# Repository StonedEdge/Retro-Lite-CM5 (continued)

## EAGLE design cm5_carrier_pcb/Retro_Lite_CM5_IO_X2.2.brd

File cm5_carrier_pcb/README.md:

# Retro Lite CM5 Carrier Board v1.1 

## What is this folder?
Note: The current files are now tested and verified to work with Radxa v2.2 carrier boards. **Also now verified to work Radxa V2.21 boards!**

This folder contains the BOM, EAGLE schematic (.sch) and board (.brd) files, as well as pick & place files to order the board with JLCPCB or your fab of choice. 
The main carrier board is a 6-layer board and you should order the board with impedance matching, according to the JLC06081H-2116 (Standard) stackup offering (0.8mm thickness). 
Currently, this version is only compatible with the Radxa CM5 (version X2.2/X2.21) & I have not tested it with other SoMs, like the Raspberry Pi CM4. 

Expect to pay around $250 per board to have it fabbed and turnkeyed with JLCPCB.

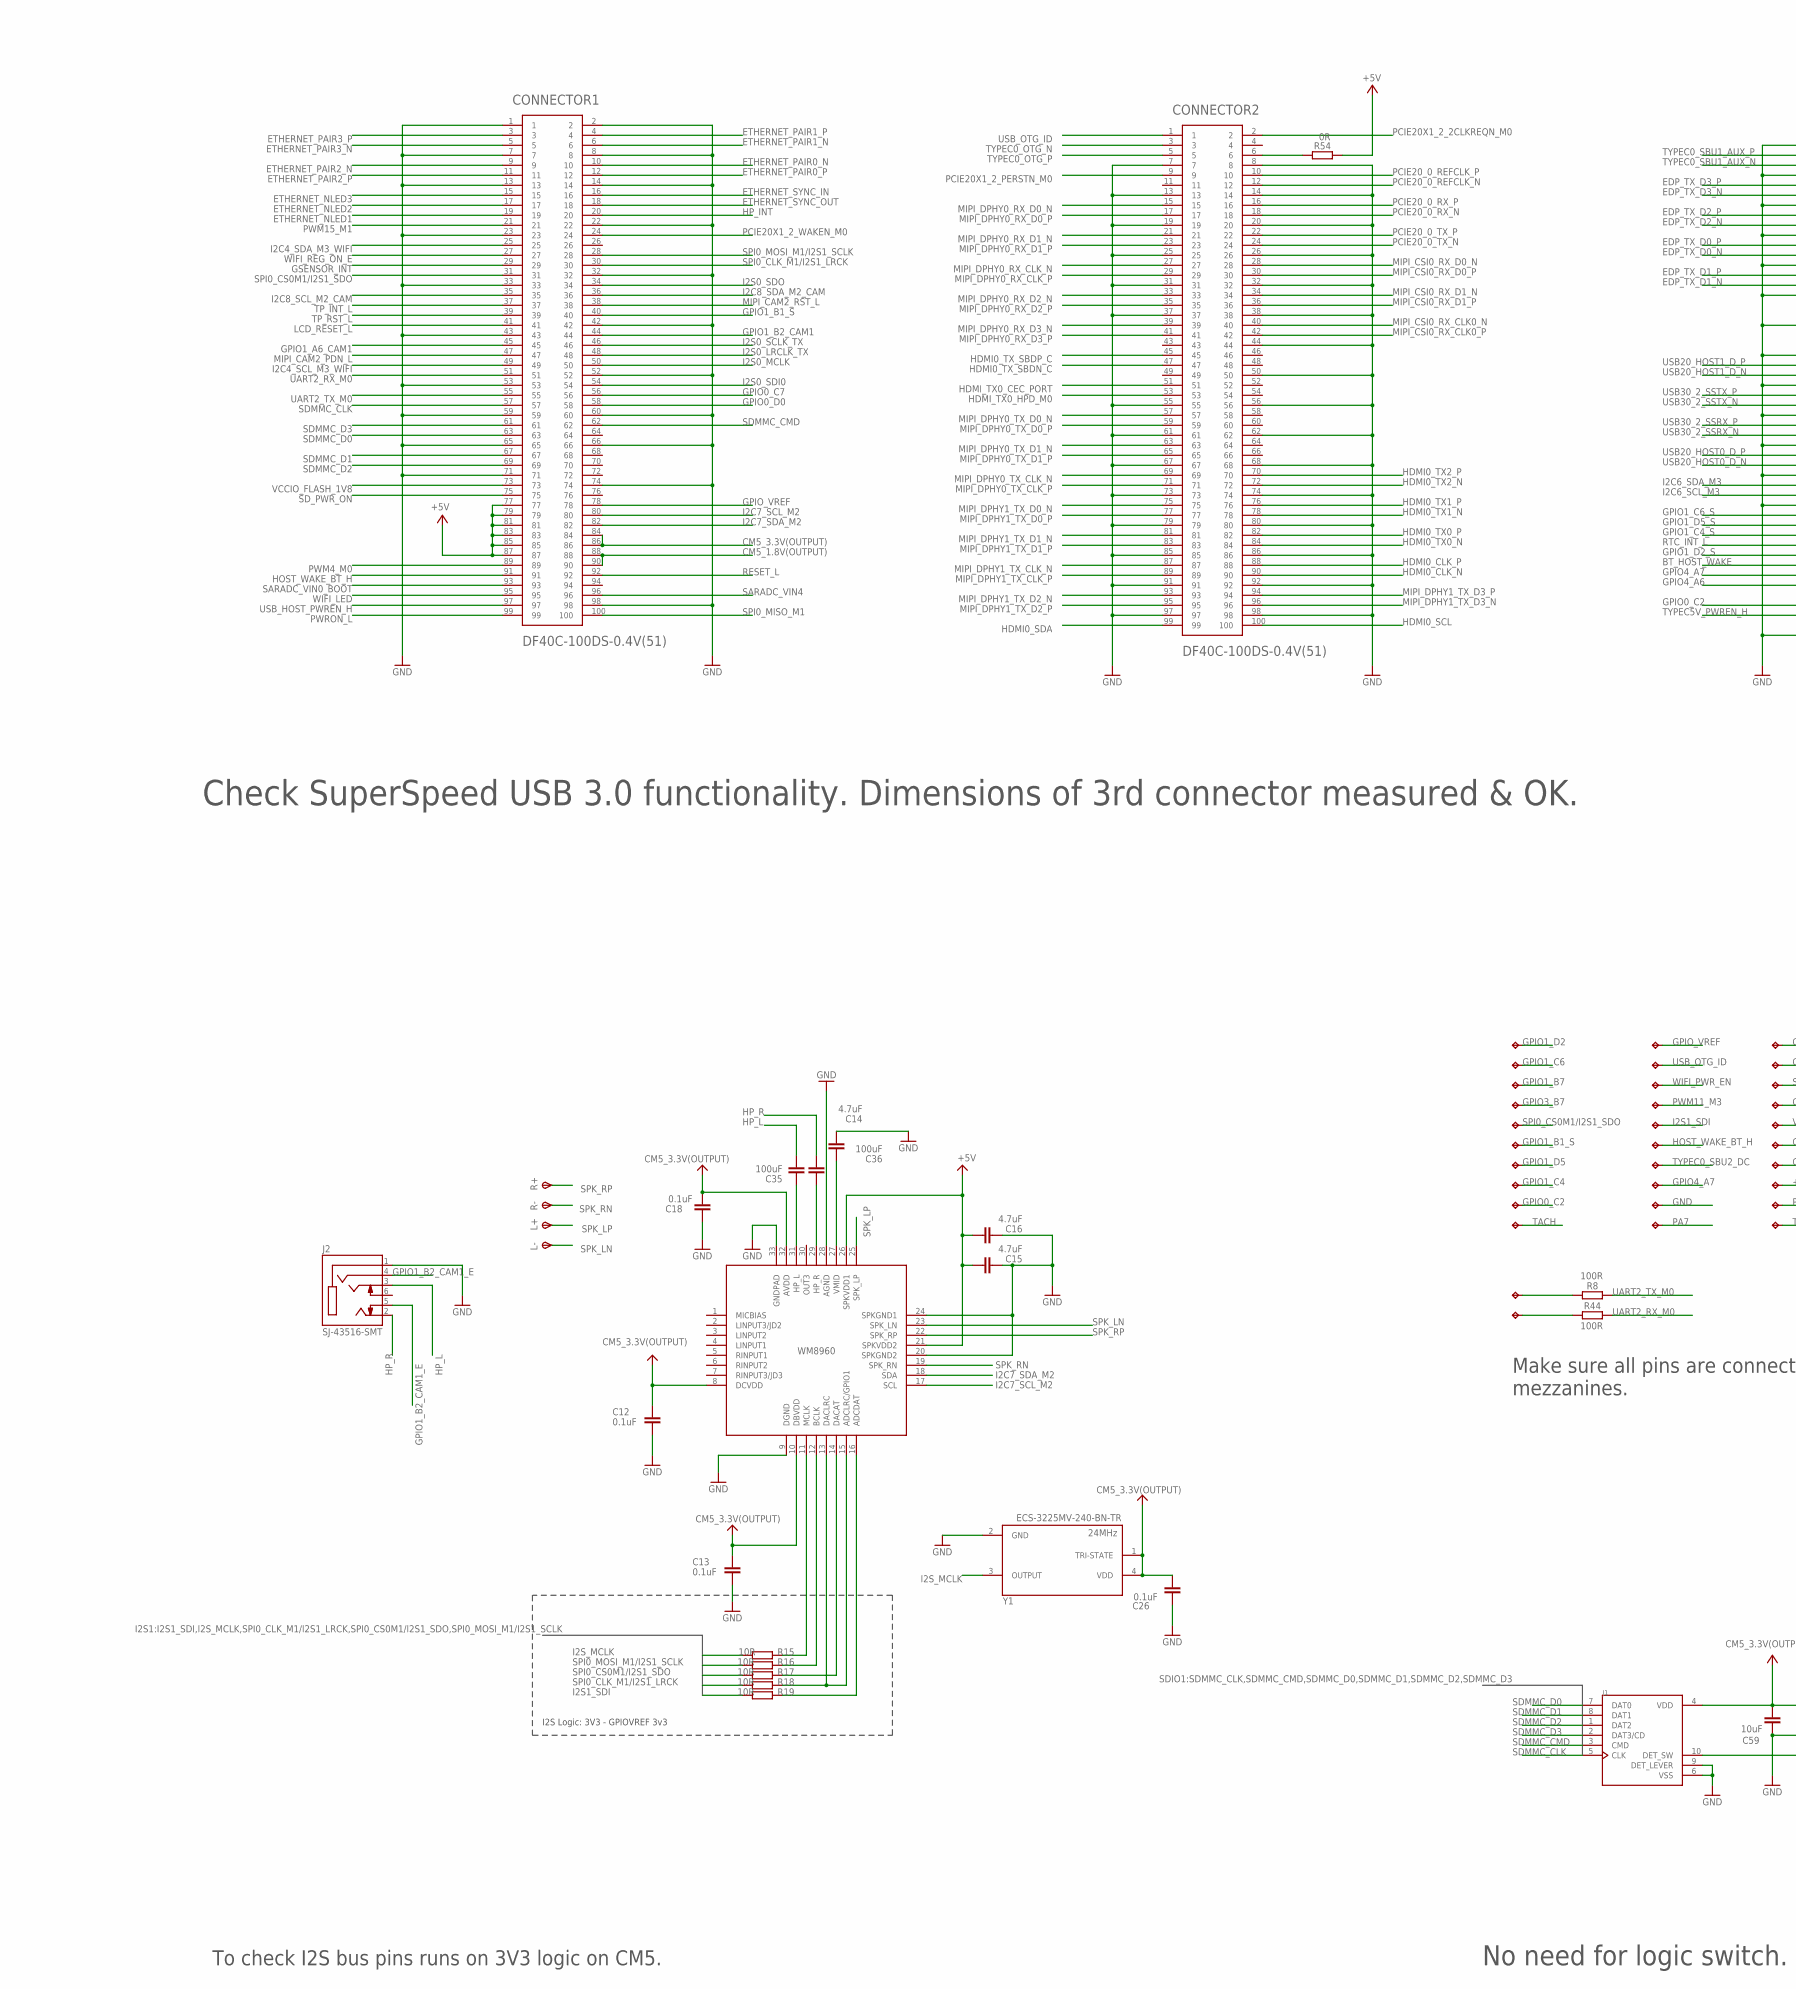
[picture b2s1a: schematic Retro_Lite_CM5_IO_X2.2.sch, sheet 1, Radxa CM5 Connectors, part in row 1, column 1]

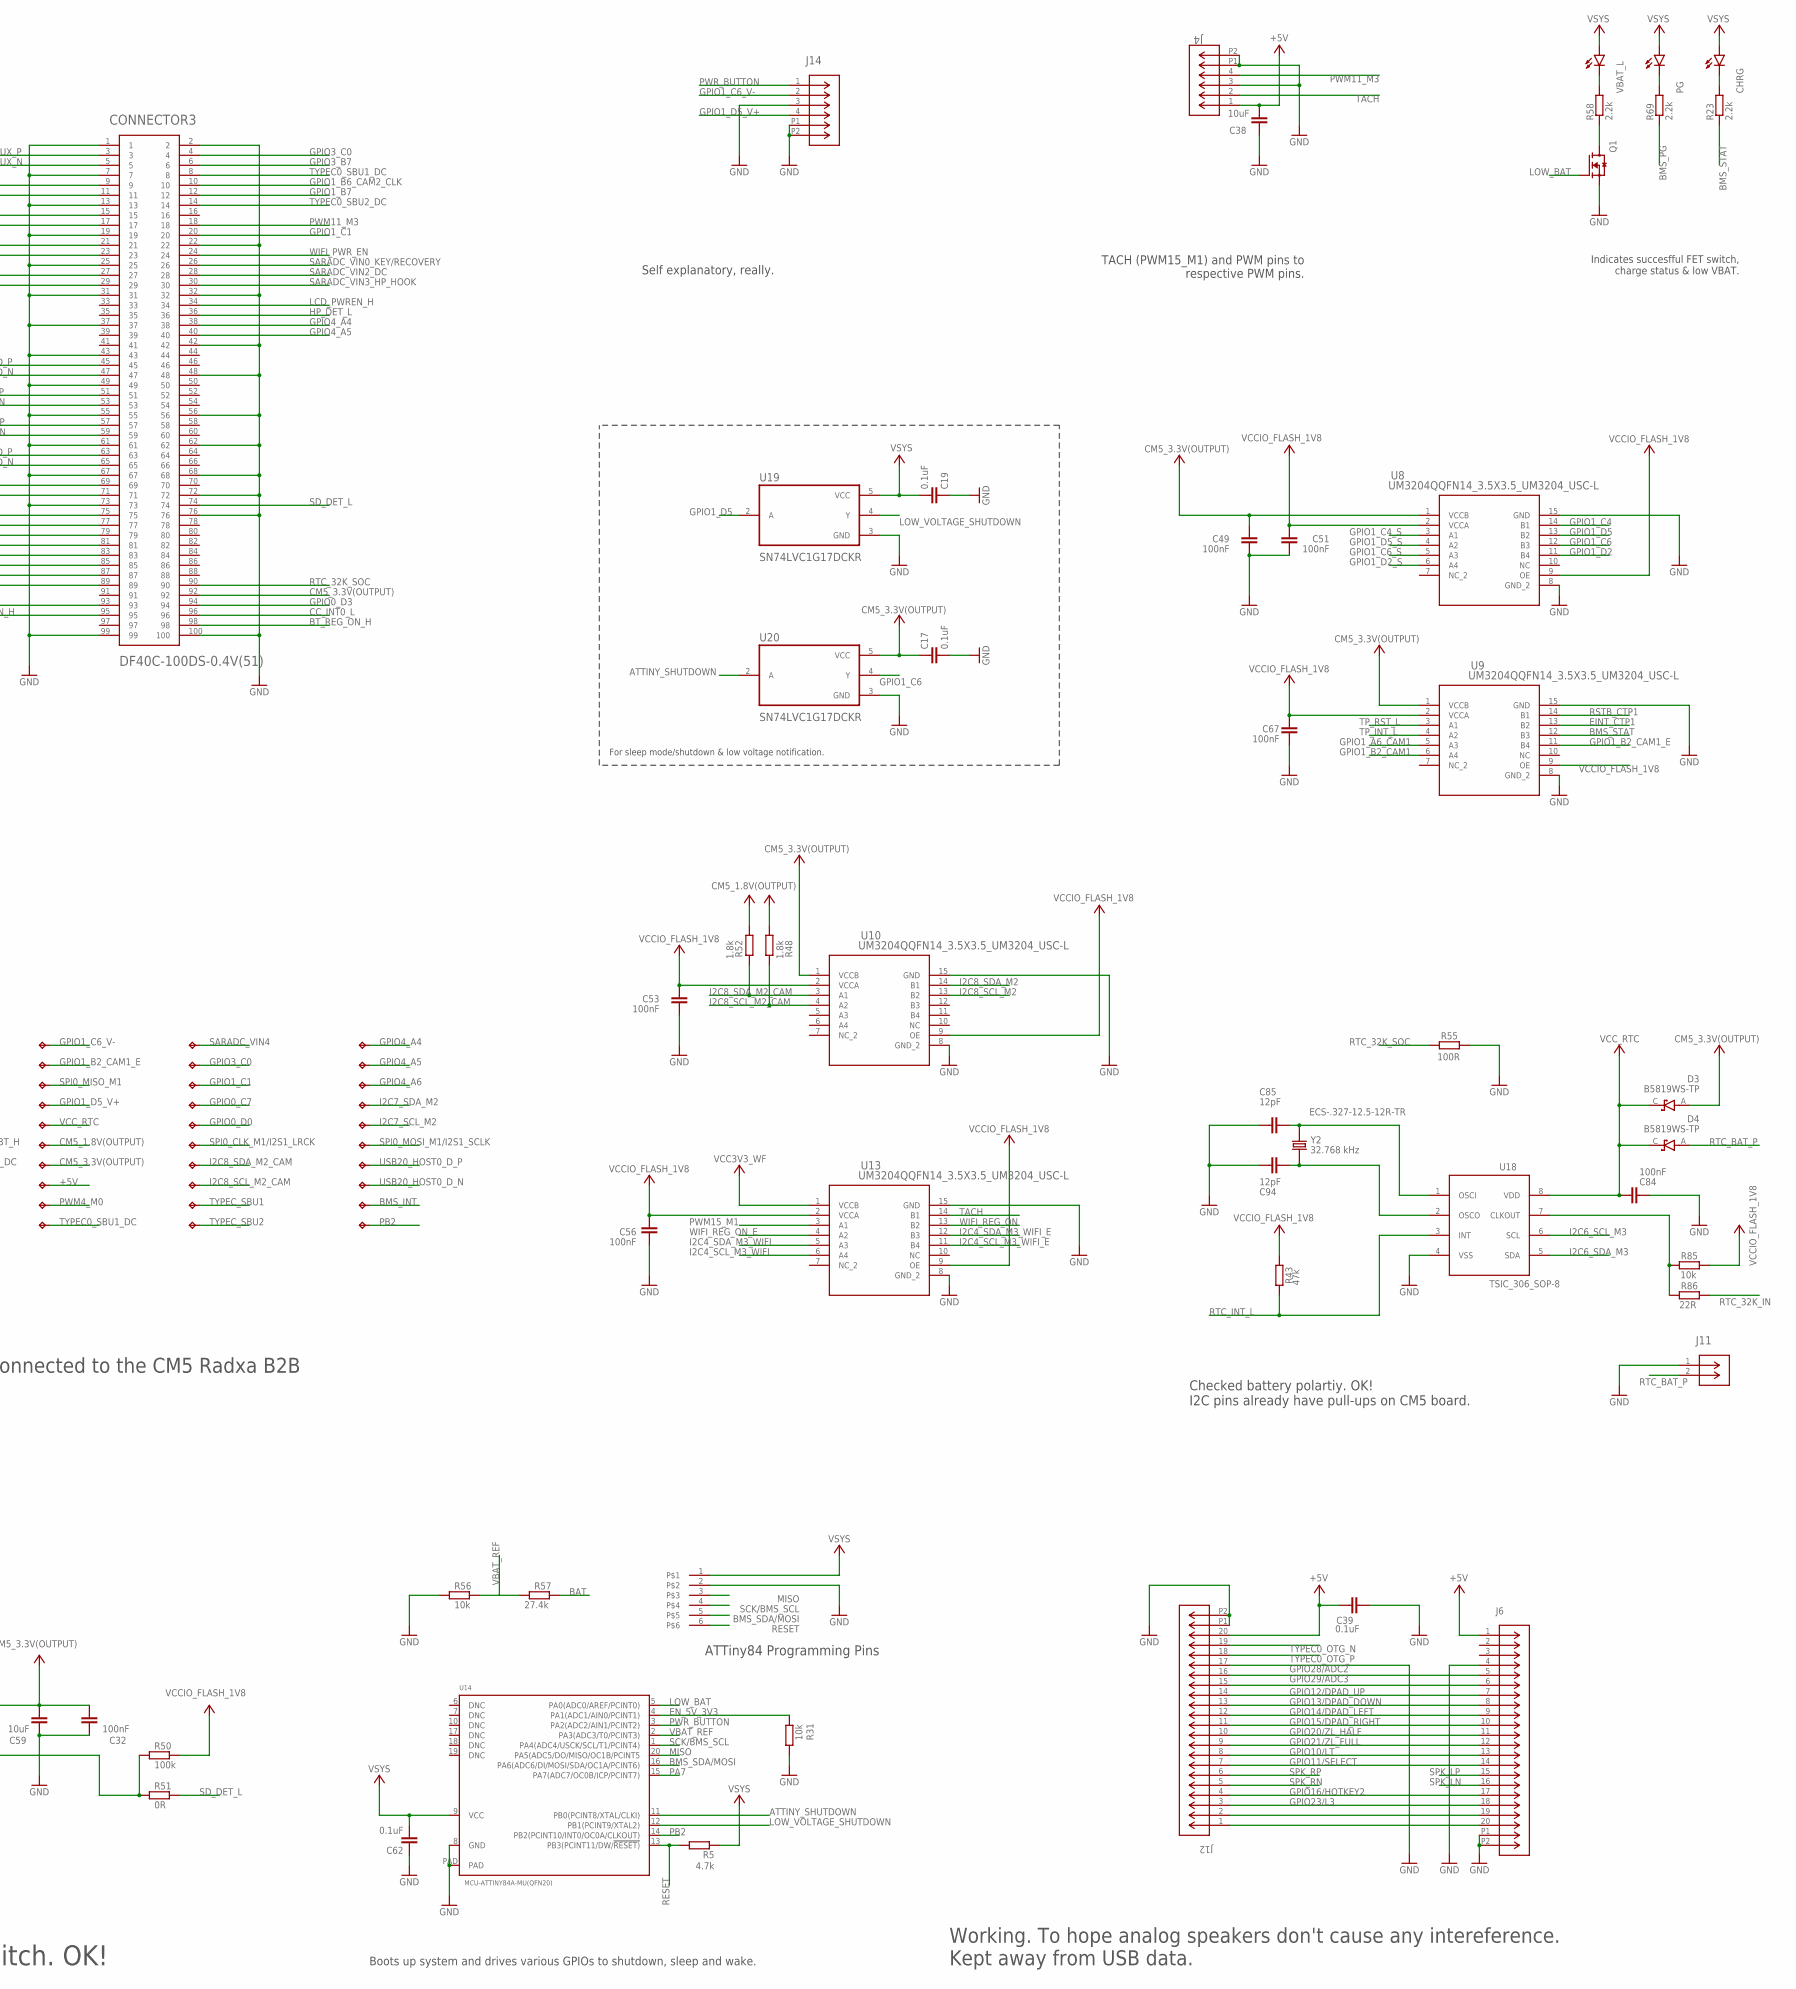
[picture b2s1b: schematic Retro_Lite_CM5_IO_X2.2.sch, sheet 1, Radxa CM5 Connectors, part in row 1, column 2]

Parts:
1V8_SCL, 1V8_SDA, 3V3_SCL, 3V3_SDA: TPTP07R; TP07R
+5V: TPTP07R; TP07R
BMS_INT: TPTP07R; TP07R
BT_DIS: TPTP07R; TP07R
C12, C13, C18, C26: 0.1uF; C0603
C14, C15, C16: 4.7uF; C0603
C17, C19, C39, C62: 0.1uF; C0402
C32, C49, C51, C53, C56, C67, C84, C94: 100nF; C0402
C35, C36: 100uF; C1206
C38: 10uF; 0805
C59: 10uF; C0402
C85: 12pF; C0402
CHRG: LEDSML0603; SML0603
CM5_1V8, CM5_3.3V: TPTP07R; TP07R
CONNECTOR1, CONNECTOR2, CONNECTOR3: DF40C-100DS-0.4V(51); HRS_DF40C-100DS-0.4V(51)
D3, D4: B5819WS-TP; SOD2512X115N
GND: TPTP07R; TP07R
GPIO0_C2, GPIO0_C7, GPIO0_D0, GPIO1_B1, GPIO1_B7, GPIO1_C1, GPIO1_C4, GPIO1_C6, GPIO1_C6_V-, GPIO1_D2, GPIO1_D5, GPIO1_D5_V+, GPIO3_B7, GPIO3_C0, GPIO4_A4, GPIO4_A5, GPIO4_A6, GPIO4_A7, GPIO14_HPD: TPTP07R; TP07R
GPIO_VREF: TPTP07R; TP07R
I2S1_LRCK, I2S1_SCLK, I2S1_SDI, I2S1_SDO: TPTP07R; TP07R
J1: 5025700893; MOLEX_5025700893
J2: SJ-43516-SMT; CUI_SJ-43516-SMT
J4, J14: 5051100492; CON_5051100492_MOL
J6, J12: 5034802000; CON_5034802000_MOL
J11: 1072TR; CONN_1072TR_KEY
L+: TPSTP09SQ; TP09SQ
L-: TPSTP09SQ; TP09SQ
NEXTRST: TPTP07R; TP07R
PB0, PB1: TPTP07R; TP07R
PG: LEDSML0603; SML0603
PWM_CTRL: TPTP07R; TP07R
Q1: AO3400A; SOT95P280X125-3N
R5: 4.7k; R0402
R8, R44, R55: 100R; R0402
R15, R16, R17, R18, R19: 10R; R0603
R23, R58, R69: 2.2k; R0402
R31, R56, R85: 10k; R0402
R43: 47k; R0402
R48, R52: 1.8k; R0402
R50: 100k; R0402
R51, R54: 0R; R0402
R57: 27.4k; R0402
R86: 22R; R0402
R+: TPSTP09SQ; TP09SQ
R-: TPSTP09SQ; TP09SQ
SARADC_VIN4: TPTP07R; TP07R
SBU1, SBU1_DC, SBU2, SBU2_DC: TPTP07R; TP07R
TACH: TPTP07R; TP07R
U6: WM8960; QFN50P500X500X100-33N
U8, U9, U10, U13: UM3204QQFN14_3.5X3.5_UM3204_USC-L; QFN14_3.5X3.5_UM3204_USC-L
U14: MCU-ATTINY84A-MU(QFN20); QFN20G-0.5-4X4MM
U18: TSIC_306_SOP-8; SOIC127P602X173-8N
U19, U20: SN74LVC1G17DCKR; SOT65P210X110-5N
U$3: 6PINEADER; 1MM_PIC-PROGRAMING_HEADER
UART2_RX_M0, UART2_TX_M0: TPTP07R; TP07R
USB20_HOST0_N, USB20_HOST0_P: TPTP07R; TP07R
USB_OTG_ID: TPTP07R; TP07R
VBAT_L: LEDSML0603; SML0603
VCC_RTC: TPTP07R; TP07R
WIFI_PWR_EN: TPTP07R; TP07R
WL_DIS/PWM4_M0: TPTP07R; TP07R
Y1: ECS-3225MV-240-BN-TR; OSC_ECS-2333-160-BN-TR
Y2: ECS-.327-12.5-12R-TR; XTAL_ECS-.327-12.5-12R-TR

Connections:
3V3: J6.19, J12.2
+5V: +5V.TP, C15.1, C16.1, C38.2, C39.1, CONNECTOR1.77, CONNECTOR1.79, CONNECTOR1.81, CONNECTOR1.83, CONNECTOR1.85, CONNECTOR1.87, J4.1, J6.1, J12.20, R54.2, U6.21 (SPKVDD2), U6.26 (SPKVDD1); also elsewhere on the board
ADC: R19.2, U6.16 (ADCDAT)
ATTINY_SHUTDOWN: U14.11 (PB0(PCINT8/XTAL/CLKI)), U20.2 (A)
BAT: R57.2; also elsewhere on the board
BCLK: R16.2, U6.12 (BCLK)
BMS_INT: BMS_INT.TP; also elsewhere on the board
BMS_PG: R69.1
BMS_SDA/MOSI: U14.16 (PA6(ADC6/DI/MOSI/SDA/OC1A/PCINT6)), U$3.5; also elsewhere on the board
BMS_STAT: R23.1, U9.12 (B3); also elsewhere on the board
BT_HOST_WAKE: CONNECTOR3.85; also elsewhere on the board
BT_REG_ON_H: CONNECTOR3.98; also elsewhere on the board
CC_INT0_L: CONNECTOR3.96
CM5_1.8V(OUTPUT): CM5_1V8.TP, CONNECTOR1.88, CONNECTOR1.90, R48.2, R52.2; also elsewhere on the board
CM5_3.3V(OUTPUT): C12.1, C13.1, C17.1, C18.2, C26.2, C32.2, C49.2, C59.2, CM5_3.3V.TP, CONNECTOR1.84, CONNECTOR1.86, CONNECTOR3.92, D3.A, J1.4 (VDD), U6.8 (DCVDD), U6.10 (DBVDD), U6.32 (AVDD), U8.1 (VCCB), U9.1 (VCCB), U10.1 (VCCB), U20.5 (VCC), Y1.1 (TRI-STATE), Y1.4 (VDD); also elsewhere on the board
DAC: R17.2, U6.14 (DACAT)
EDP_TX_D0_N: CONNECTOR3.23; also elsewhere on the board
EDP_TX_D0_P: CONNECTOR3.21; also elsewhere on the board
EDP_TX_D1_N: CONNECTOR3.29; also elsewhere on the board
EDP_TX_D1_P: CONNECTOR3.27; also elsewhere on the board
EDP_TX_D2_N: CONNECTOR3.17; also elsewhere on the board
EDP_TX_D2_P: CONNECTOR3.15; also elsewhere on the board
EDP_TX_D3_N: CONNECTOR3.11; also elsewhere on the board
EDP_TX_D3_P: CONNECTOR3.9; also elsewhere on the board
EINT_CTP1: U9.13 (B2); also elsewhere on the board
EN_5V_3V3: R31.2, U14.4 (PA1(ADC1/AIN0/PCINT1)); also elsewhere on the board
ETHERNET_NLED1: CONNECTOR1.19
ETHERNET_NLED2: CONNECTOR1.17
ETHERNET_NLED3: CONNECTOR1.15
ETHERNET_PAIR0_N: CONNECTOR1.10
ETHERNET_PAIR0_P: CONNECTOR1.12
ETHERNET_PAIR1_N: CONNECTOR1.6
ETHERNET_PAIR1_P: CONNECTOR1.4
ETHERNET_PAIR2_N: CONNECTOR1.9
ETHERNET_PAIR2_P: CONNECTOR1.11
ETHERNET_PAIR3_N: CONNECTOR1.5
ETHERNET_PAIR3_P: CONNECTOR1.3
ETHERNET_SYNC_IN: CONNECTOR1.16
ETHERNET_SYNC_OUT: CONNECTOR1.18
GND: C12.2, C13.2, C14.2, C15.2, C16.2, C17.2, C18.1, C19.1, C26.1, C32.1, C38.1, C39.2, C49.1, C51.1, C53.1, C56.1, C59.1, C62.1, C67.1, C84.1, C85.2, C94.2, CONNECTOR1.1, CONNECTOR1.2, CONNECTOR1.7, CONNECTOR1.8, CONNECTOR1.13, CONNECTOR1.14, CONNECTOR1.22, CONNECTOR1.23, CONNECTOR1.32, CONNECTOR1.33, CONNECTOR1.42, CONNECTOR1.43, CONNECTOR1.52, CONNECTOR1.53, CONNECTOR1.59, CONNECTOR1.60, CONNECTOR1.65, CONNECTOR1.66, CONNECTOR1.71, CONNECTOR1.74, CONNECTOR1.98, CONNECTOR2.7, CONNECTOR2.8, CONNECTOR2.13, CONNECTOR2.14, CONNECTOR2.19, CONNECTOR2.20, CONNECTOR2.25, CONNECTOR2.26, CONNECTOR2.31, CONNECTOR2.32, CONNECTOR2.37, CONNECTOR2.38, CONNECTOR2.44, CONNECTOR2.50, CONNECTOR2.55, CONNECTOR2.56, CONNECTOR2.61, CONNECTOR2.62, CONNECTOR2.67, CONNECTOR2.68, CONNECTOR2.73, CONNECTOR2.74, CONNECTOR2.79, CONNECTOR2.80, CONNECTOR2.85, CONNECTOR2.86, CONNECTOR2.91, CONNECTOR2.92, CONNECTOR2.97, CONNECTOR2.98, CONNECTOR3.1, CONNECTOR3.2, CONNECTOR3.7, CONNECTOR3.13, CONNECTOR3.19, CONNECTOR3.22, CONNECTOR3.25, CONNECTOR3.31, CONNECTOR3.32, CONNECTOR3.37, CONNECTOR3.42, CONNECTOR3.43, CONNECTOR3.48, CONNECTOR3.49, CONNECTOR3.55, CONNECTOR3.56, CONNECTOR3.61, CONNECTOR3.62, CONNECTOR3.67, CONNECTOR3.68, CONNECTOR3.72, CONNECTOR3.73, CONNECTOR3.76, CONNECTOR3.99, CONNECTOR3.100, GND.TP, J1.6 (VSS), J1.9 (DET_LEVER), J2.1 (SLEEVE), J4.3, J4.P1, J4.P2, J6.4, J6.P1, J6.P2, J11.1, J12.17, J12.P1, J12.P2, J14.3, J14.P1, J14.P2, Q1.2 (S), R31.1, R55.2, R56.1, U6.9 (DGND), U6.20 (SPKGND2), U6.24 (SPKGND1), U6.28 (AGND), U6.33 (GNDPAD), U8.8 (GND_2), U8.15 (GND), U9.8 (GND_2), U9.15 (GND), U10.8 (GND_2), U10.15 (GND), U13.8 (GND_2), U13.15 (GND), U14.8 (GND), U14.PAD, U18.4 (VSS), U19.3 (GND), U20.3 (GND), U$3.2, Y1.2 (GND); also elsewhere on the board
GPIO0_C2: CONNECTOR3.93, GPIO0_C2.TP
GPIO0_C7: CONNECTOR1.56, GPIO0_C7.TP; also elsewhere on the board
GPIO0_D0: CONNECTOR1.58, GPIO0_D0.TP
GPIO0_D3: CONNECTOR3.94; also elsewhere on the board
GPIO1_A6_CAM1: CONNECTOR1.45, U9.5 (A3)
GPIO1_B1_S: CONNECTOR1.40, GPIO1_B1.TP
GPIO1_B2_CAM1: CONNECTOR1.44, U9.6 (A4)
GPIO1_B2_CAM1_E: GPIO14_HPD.TP, J2.4 (RING2), J2.5 (TIP_SWITCH), U9.11 (B4)
GPIO1_B6_CAM2_CLK: CONNECTOR3.10
GPIO1_B7: CONNECTOR3.12, GPIO1_B7.TP
GPIO1_C1: CONNECTOR3.20, GPIO1_C1.TP
GPIO1_C4: GPIO1_C4.TP, U8.14 (B1); also elsewhere on the board
GPIO1_C4_S: CONNECTOR3.79, U8.3 (A1)
GPIO1_C6: GPIO1_C6.TP, U8.12 (B3), U20.4 (Y)
GPIO1_C6_S: CONNECTOR3.75, U8.5 (A3)
GPIO1_C6_V-: GPIO1_C6_V-.TP, J14.2
GPIO1_D2: GPIO1_D2.TP, U8.11 (B4); also elsewhere on the board
GPIO1_D2_S: CONNECTOR3.83, U8.6 (A4)
GPIO1_D5: GPIO1_D5.TP, U8.13 (B2), U19.2 (A)
GPIO1_D5_S: CONNECTOR3.77, U8.4 (A2)
GPIO1_D5_V+: GPIO1_D5_V+.TP, J14.4
GPIO3_B7: CONNECTOR3.6, GPIO3_B7.TP
GPIO3_C0: CONNECTOR3.4, GPIO3_C0.TP
GPIO4_A4: CONNECTOR3.38, GPIO4_A4.TP
GPIO4_A5: CONNECTOR3.40, GPIO4_A5.TP
GPIO4_A6: CONNECTOR3.89, GPIO4_A6.TP
GPIO4_A7: CONNECTOR3.87, GPIO4_A7.TP
GPIO10/LT: J6.13, J12.8
GPIO11/SELECT: J6.14, J12.7
GPIO12/DPAD_UP: J6.7, J12.14
GPIO13/DPAD_DOWN: J6.8, J12.13
GPIO14/DPAD_LEFT: J6.9, J12.12
GPIO15/DPAD_RIGHT: J6.10, J12.11
GPIO16/HOTKEY2: J6.17, J12.4
GPIO20/ZL_HALF: J6.11, J12.10
GPIO21/ZL_FULL: J6.12, J12.9
GPIO23/L3: J6.18, J12.3
GPIO28/ADC2: J6.5, J12.16
GPIO29/ADC3: J6.6, J12.15
GPIO_VREF: CONNECTOR1.78, GPIO_VREF.TP
GSENSOR_INT: CONNECTOR1.29; also elsewhere on the board
HDMI0_CLK_N: CONNECTOR2.90; also elsewhere on the board
HDMI0_CLK_P: CONNECTOR2.88; also elsewhere on the board
HDMI0_SCL: CONNECTOR2.100; also elsewhere on the board
HDMI0_SDA: CONNECTOR2.99; also elsewhere on the board
HDMI0_TX0_N: CONNECTOR2.84; also elsewhere on the board
HDMI0_TX0_P: CONNECTOR2.82; also elsewhere on the board
HDMI0_TX1_N: CONNECTOR2.78; also elsewhere on the board
HDMI0_TX1_P: CONNECTOR2.76; also elsewhere on the board
HDMI0_TX2_N: CONNECTOR2.72; also elsewhere on the board
HDMI0_TX2_P: CONNECTOR2.70; also elsewhere on the board
HDMI0_TX_SBDN_C: CONNECTOR2.47; also elsewhere on the board
HDMI0_TX_SBDP_C: CONNECTOR2.45; also elsewhere on the board
HDMI_TX0_CEC_PORT: CONNECTOR2.51; also elsewhere on the board
HDMI_TX0_HPD_M0: CONNECTOR2.53; also elsewhere on the board
HOST_WAKE_BT_H: BT_DIS.TP, CONNECTOR1.91; also elsewhere on the board
HP_DET_L: CONNECTOR3.36
HP_INT: CONNECTOR1.20
HP_L: C35.2, J2.3 (RING1)
HP_R: C36.2, J2.2 (TIP)
I2C4_SCL_M3_WIFI: CONNECTOR1.49, U13.6 (A4)
I2C4_SCL_M3_WIFI_E: U13.11 (B4); also elsewhere on the board
I2C4_SDA_M3_WIFI: CONNECTOR1.25, U13.5 (A3)
I2C4_SDA_M3_WIFI_E: U13.12 (B3); also elsewhere on the board
I2C6_SCL_M3: CONNECTOR3.71, U18.6 (SCL)
I2C6_SDA_M3: CONNECTOR3.69, U18.5 (SDA)
I2C7_SCL_M2: 3V3_SCL.TP, CONNECTOR1.80, U6.17 (SCL); also elsewhere on the board
I2C7_SDA_M2: 3V3_SDA.TP, CONNECTOR1.82, U6.18 (SDA); also elsewhere on the board
I2C8_SCL_M2: U10.13 (B2); also elsewhere on the board
I2C8_SCL_M2_CAM: 1V8_SCL.TP, CONNECTOR1.35, R48.1, U10.4 (A2)
I2C8_SDA_M2: U10.14 (B1); also elsewhere on the board
I2C8_SDA_M2_CAM: 1V8_SDA.TP, CONNECTOR1.36, R52.1, U10.3 (A1)
I2S0_LRCLK_TX: CONNECTOR1.48
I2S0_MCLK: CONNECTOR1.50
I2S0_SCLK_TX: CONNECTOR1.46
I2S0_SDI0: CONNECTOR1.54
I2S0_SDO: CONNECTOR1.34
I2S1_SDI: I2S1_SDI.TP, R19.1
I2S_MCLK: R15.1, Y1.3 (OUTPUT)
LCD_PWREN_H: CONNECTOR3.34
LCD_RESET_L: CONNECTOR1.41; also elsewhere on the board
LOW_BAT: Q1.1 (G), U14.5 (PA0(ADC0/AREF/PCINT0))
LOW_VOLTAGE_SHUTDOWN: U14.12 (PB1(PCINT9/XTAL2)), U19.4 (Y)
MCLK: R15.2, U6.11 (MCLK)
MIPI_CAM2_PDN_L: CONNECTOR1.47
MIPI_CAM2_RST_L: CONNECTOR1.38
MIPI_CSI0_RX_CLK0_N: CONNECTOR2.40
MIPI_CSI0_RX_CLK0_P: CONNECTOR2.42
MIPI_CSI0_RX_D0_N: CONNECTOR2.28
MIPI_CSI0_RX_D0_P: CONNECTOR2.30
MIPI_CSI0_RX_D1_N: CONNECTOR2.34
MIPI_CSI0_RX_D1_P: CONNECTOR2.36
MIPI_DPHY0_RX_CLK_N: CONNECTOR2.27
MIPI_DPHY0_RX_CLK_P: CONNECTOR2.29
MIPI_DPHY0_RX_D0_N: CONNECTOR2.15
MIPI_DPHY0_RX_D0_P: CONNECTOR2.17
MIPI_DPHY0_RX_D1_N: CONNECTOR2.21
MIPI_DPHY0_RX_D1_P: CONNECTOR2.23
MIPI_DPHY0_RX_D2_N: CONNECTOR2.33
MIPI_DPHY0_RX_D2_P: CONNECTOR2.35
MIPI_DPHY0_RX_D3_N: CONNECTOR2.39
MIPI_DPHY0_RX_D3_P: CONNECTOR2.41
MIPI_DPHY0_TX_CLK_N: CONNECTOR2.69
MIPI_DPHY0_TX_CLK_P: CONNECTOR2.71
MIPI_DPHY0_TX_D0_N: CONNECTOR2.57
MIPI_DPHY0_TX_D0_P: CONNECTOR2.59
MIPI_DPHY0_TX_D1_N: CONNECTOR2.63
MIPI_DPHY0_TX_D1_P: CONNECTOR2.65
MIPI_DPHY1_TX_CLK_N: CONNECTOR2.87; also elsewhere on the board
MIPI_DPHY1_TX_CLK_P: CONNECTOR2.89; also elsewhere on the board
MIPI_DPHY1_TX_D0_N: CONNECTOR2.75; also elsewhere on the board
MIPI_DPHY1_TX_D0_P: CONNECTOR2.77; also elsewhere on the board
MIPI_DPHY1_TX_D1_N: CONNECTOR2.81; also elsewhere on the board
MIPI_DPHY1_TX_D1_P: CONNECTOR2.83; also elsewhere on the board
MIPI_DPHY1_TX_D2_N: CONNECTOR2.93; also elsewhere on the board
MIPI_DPHY1_TX_D2_P: CONNECTOR2.95; also elsewhere on the board
MIPI_DPHY1_TX_D3_N: CONNECTOR2.96; also elsewhere on the board
MIPI_DPHY1_TX_D3_P: CONNECTOR2.94; also elsewhere on the board
MISO: U14.20 (PA5(ADC5/DO/MISO/OC1B/PCINT5), U$3.3
unnamed: C14.1, U6.27 (VMID)
unnamed: C35.1, U6.31 (HP_L)
unnamed: C36.1, U6.29 (HP_R)
unnamed: J6.20, J12.1
unnamed: J1.10 (DET_SW), R50.1, R51.1
unnamed: R8.1, UART2_TX_M0.TP
unnamed: R44.1, UART2_RX_M0.TP
unnamed: CONNECTOR2.6, R54.1
unnamed: R58.2, VBAT_L.C
unnamed: R85.1, R86.1, U18.7 (CLKOUT)
unnamed: Q1.3 (D), R58.1
unnamed: CHRG.C, R23.2
unnamed: C94.1, U18.2 (OSCO), Y2.1
unnamed: C85.1, U18.1 (OSCI), Y2.2
unnamed: PG.C, R69.2
PA7: PB1.TP, U14.15 (PA7(ADC7/OC0B/ICP/PCINT7))
PB2: PB0.TP, U14.14 (PB2(PCINT10/INT0/OC0A/CLKOUT))
PCIE20X1_2_2CLKREQN_M0: CONNECTOR2.2; also elsewhere on the board
PCIE20X1_2_PERSTN_M0: CONNECTOR2.9; also elsewhere on the board
PCIE20X1_2_WAKEN_M0: CONNECTOR1.24; also elsewhere on the board
PCIE20_0_REFCLK_N: CONNECTOR2.12; also elsewhere on the board
PCIE20_0_REFCLK_P: CONNECTOR2.10; also elsewhere on the board
PCIE20_0_RX_N: CONNECTOR2.18; also elsewhere on the board
PCIE20_0_RX_P: CONNECTOR2.16; also elsewhere on the board
PCIE20_0_TX_N: CONNECTOR2.24; also elsewhere on the board
PCIE20_0_TX_P: CONNECTOR2.22; also elsewhere on the board
PWM4_M0: CONNECTOR1.89, WL_DIS/PWM4_M0.TP
PWM11_M3: CONNECTOR3.18, J4.4, PWM_CTRL.TP
PWM15_M1: CONNECTOR1.21, U13.3 (A1)
PWRON_L: CONNECTOR1.99
PWR_BUTTON: J14.1, U14.3 (PA2(ADC2/AIN1/PCINT2))
RESET: R5.2, U14.13 (PB3(PCINT11/DW/!RESET)), U$3.6
RESET_L: CONNECTOR1.92
RSTB_CTP1: U9.14 (B1); also elsewhere on the board
RTC_32K_IN: R86.2; also elsewhere on the board
RTC_32K_SOC: CONNECTOR3.90, R55.1
RTC_BAT_P: D4.A, J11.2
RTC_INT_L: CONNECTOR3.81, R43.2, U18.3 (INT)
SARADC_VIN0_BOOT: CONNECTOR1.93
SARADC_VIN0_KEY/RECOVERY: CONNECTOR3.26
SARADC_VIN2_DC: CONNECTOR3.28
SARADC_VIN3_HP_HOOK: CONNECTOR3.30
SARADC_VIN4: CONNECTOR1.96, SARADC_VIN4.TP
SCK/BMS_SCL: U14.1 (PA4(ADC4/USCK/SCL/T1/PCINT4)), U$3.4; also elsewhere on the board
SDMMC_CLK: CONNECTOR1.57, J1.5 (CLK)
SDMMC_CMD: CONNECTOR1.62, J1.3 (CMD)
SDMMC_D0: CONNECTOR1.63, J1.7 (DAT0)
SDMMC_D1: CONNECTOR1.67, J1.8 (DAT1)
SDMMC_D2: CONNECTOR1.69, J1.1 (DAT2)
SDMMC_D3: CONNECTOR1.61, J1.2 (DAT3/CD)
SD_DET_L: CONNECTOR3.74, R51.2
SD_PWR_ON: CONNECTOR1.75; also elsewhere on the board
SPI0_CLK_M1/I2S1_LRCK: CONNECTOR1.30, I2S1_LRCK.TP, R18.1
SPI0_CS0M1/I2S1_SDO: CONNECTOR1.31, I2S1_SDO.TP, R17.1
SPI0_MISO_M1: CONNECTOR1.100, NEXTRST.TP
SPI0_MOSI_M1/I2S1_SCLK: CONNECTOR1.28, I2S1_SCLK.TP, R16.1
SPK_LN: J6.16, L-.TP, U6.23 (SPK_LN)
SPK_LP: J6.15, L+.TP, U6.25 (SPK_LP)
SPK_RN: J12.5, R-.TP, U6.19 (SPK_RN)
SPK_RP: J12.6, R+.TP, U6.22 (SPK_RP)
TACH: J4.2, TACH.TP, U13.14 (B1)
TP_INT_L: CONNECTOR1.37, U9.4 (A2)
TP_RST_L: CONNECTOR1.39, U9.3 (A1)
TYPEC0_OTG_N: CONNECTOR2.3, J12.19
TYPEC0_OTG_P: CONNECTOR2.5, J12.18
TYPEC0_SBU1_AUX_N: CONNECTOR3.5; also elsewhere on the board
TYPEC0_SBU1_AUX_P: CONNECTOR3.3; also elsewhere on the board
TYPEC0_SBU1_DC: CONNECTOR3.8, SBU1_DC.TP
TYPEC0_SBU2_DC: CONNECTOR3.14, SBU2_DC.TP
TYPEC5V_PWREN_H: CONNECTOR3.95
TYPEC_SBU1: SBU1.TP; also elsewhere on the board
TYPEC_SBU2: SBU2.TP; also elsewhere on the board
UART2_RX_M0: CONNECTOR1.51, R44.2
UART2_TX_M0: CONNECTOR1.55, R8.2
USB20_HOST0_D_N: CONNECTOR3.65, USB20_HOST0_N.TP; also elsewhere on the board
USB20_HOST0_D_P: CONNECTOR3.63, USB20_HOST0_P.TP; also elsewhere on the board
USB20_HOST1_D_N: CONNECTOR3.47; also elsewhere on the board
USB20_HOST1_D_P: CONNECTOR3.45; also elsewhere on the board
USB30_2_SSRX_N: CONNECTOR3.59; also elsewhere on the board
USB30_2_SSRX_P: CONNECTOR3.57; also elsewhere on the board
USB30_2_SSTX_N: CONNECTOR3.53; also elsewhere on the board
USB30_2_SSTX_P: CONNECTOR3.51; also elsewhere on the board
USB_HOST_PWREN_H: CONNECTOR1.97
USB_OTG_ID: CONNECTOR2.1, USB_OTG_ID.TP
VBAT_REF: R56.2, R57.1, U14.2 (PA3(ADC3/T0/PCINT3))
VCC3V3_WF: U13.1 (VCCB); also elsewhere on the board
VCCIO_FLASH_1V8: C51.2, C53.2, C56.2, C67.2, CONNECTOR1.73, R43.1, R50.2, R85.2, U8.2 (VCCA), U8.9 (OE), U9.2 (VCCA), U9.9 (OE), U10.2 (VCCA), U10.9 (OE), U13.2 (VCCA), U13.9 (OE)
VCC_RTC: C84.2, D3.C (K), D4.C (K), U18.8 (VDD), VCC_RTC.TP
VSYS: C19.2, C62.2, CHRG.A, PG.A, R5.1, U14.9 (VCC), U19.5 (VCC), U$3.1, VBAT_L.A; also elsewhere on the board
WIFI_LED: CONNECTOR1.95; also elsewhere on the board
WIFI_PWR_EN: CONNECTOR3.24, WIFI_PWR_EN.TP; also elsewhere on the board
WIFI_REG_ON: U13.13 (B2); also elsewhere on the board
WIFI_REG_ON_E: CONNECTOR1.27, U13.4 (A2)
WS: R18.2, U6.13 (DACLRC), U6.15 (ADCLRC/GPIO1)

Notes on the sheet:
WM8960
24MHz
0.1uF
To check I2S bus pins runs on 3V3 logic on CM5.
Boots up system and drives various GPIOs to shutdown, sleep and wake.
Check SuperSpeed USB 3.0 functionality. Dimensions of 3rd connector measured & OK.
100nF
12pF
32.768 kHz
47k
10k
22R
Checked battery polartiy. OK! I2C pins already have pull-ups on CM5 board.
Make sure all pins are connected to the CM5 Radxa B2B mezzanines.
TACH (PWM15_M1) and PWM pins to respective PWM pins.
Indicates succesfful FET switch, charge status & low VBAT.
10uF
100R
No need for logic switch. OK!
Working. To hope analog speakers don't cause any intereference. Kept away from USB data.
ATTiny84 Programming Pins
Self explanatory, really.
I2S Logic: 3V3 - GPIOVREF 3v3
For sleep mode/shutdown & low voltage notification.
